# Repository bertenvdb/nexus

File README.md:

# Nexus

**Nexus Tools Board** and **Nexus Docks Board**: Klipper controller boards for a hotend changer with up to 8 tools.

- **Nexus Tools Board:** 8 heaters, 8 thermistors (NTC 100K / PT1000), 8 filament sensors, 1 WS2812 chain, hardware cutoff of the heater rail with startup self-test, USB + CAN.
- **Nexus Docks Board:** 9 fans (5/12/24V), 1 WS2812 chain, USB + CAN.

Both boards: STM32G0B1RBT6, Klipper + Katapult, designed in KiCad 10 for JLCPCB assembly.

Status and documentation: [`docs/README.md`](docs/README.md). Klipper configuration and macros (YUDX toolchanger): [`klipper/`](klipper/README.md). Working agreements for Claude Code: [`CLAUDE.md`](CLAUDE.md).

---

## ⚠️ Safety — read this before you build or use a board

This board drives heaters. A mistake in the design, assembly, wiring or configuration can cause a **fire**. This is a hobby project. It is **not certified**, not CE marked and not independently tested.

**Design limits**
- **24 V DC** only. Max. **70 W per heater channel** (measured at room temperature), max. 8 channels.
- Thermistors: NTC 100K or PT1000. No thermocouples or PT100.
- Only for use with **Klipper** and the included safety macros.

**Mandatory**
1. Klipper's `verify_heater` active, with sensible `max_temp` values.
2. Keep the **cutoff startup self-test** enabled (runs at every Klipper start, `NEXUS_SELFTEST`). Do not print if it fails; call `NEXUS_PRINT_START` in your `PRINT_START` so a print cannot start without it.
3. Run the **commissioning macro** `NEXUS_COMMISSION` after every (re)wiring. It checks that each heater heats the correct thermistor.
4. **Never print unattended** until the whole setup has proven itself over multiple prints.
5. One PSU, or PSUs with a common negative.
6. Check the **power cable polarity** before you plug in: on the board connector (XT60 on the Tools Board, XT30 on the Docks Board) **+ is pin 2**, marked **+** on the silkscreen. Wire your plug to match.

**Optional**
- Extra passive protection at the hotend: a PTC heater (self-limiting) and/or a thermal fuse (TCO) on the heatsink or tool holder. A TCO on the heater block itself does not work: they go up to ±240 °C, at or below print temperature.
- A smoke detector above the printer.

You build and use this design **entirely at your own risk**. See the disclaimers in the licenses.

---

## Licenses

| Part | License |
|---|---|
| Hardware (KiCad files, production files) | [CERN-OHL-S-2.0](LICENSES/CERN-OHL-S-2.0.txt) |
| Klipper macros, config, scripts | [GPL-3.0-or-later](LICENSES/GPL-3.0-or-later.txt) |
| Documentation | [CC-BY-SA-4.0](LICENSES/CC-BY-SA-4.0.txt) |

Copyright © 2026 Berten.

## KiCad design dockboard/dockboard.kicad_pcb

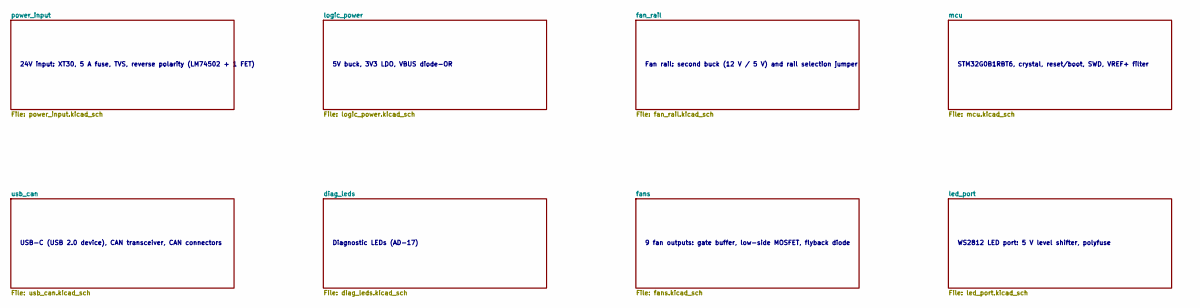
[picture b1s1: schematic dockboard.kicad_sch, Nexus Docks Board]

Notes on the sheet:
USB-C (USB 2.0 device), CAN transceiver, CAN connectors
9 fan outputs: gate buffer, low-side MOSFET, flyback diode
24V input: XT30, 5 A fuse, TVS, reverse polarity (LM74502 + 1 FET)
Diagnostic LEDs (AD-17)
Fan rail: second buck (12 V / 5 V) and rail selection jumper
WS2812 LED port: 5 V level shifter, polyfuse
STM32G0B1RBT6, crystal, reset/boot, SWD, VREF+ filter
5V buck, 3V3 LDO, VBUS diode-OR

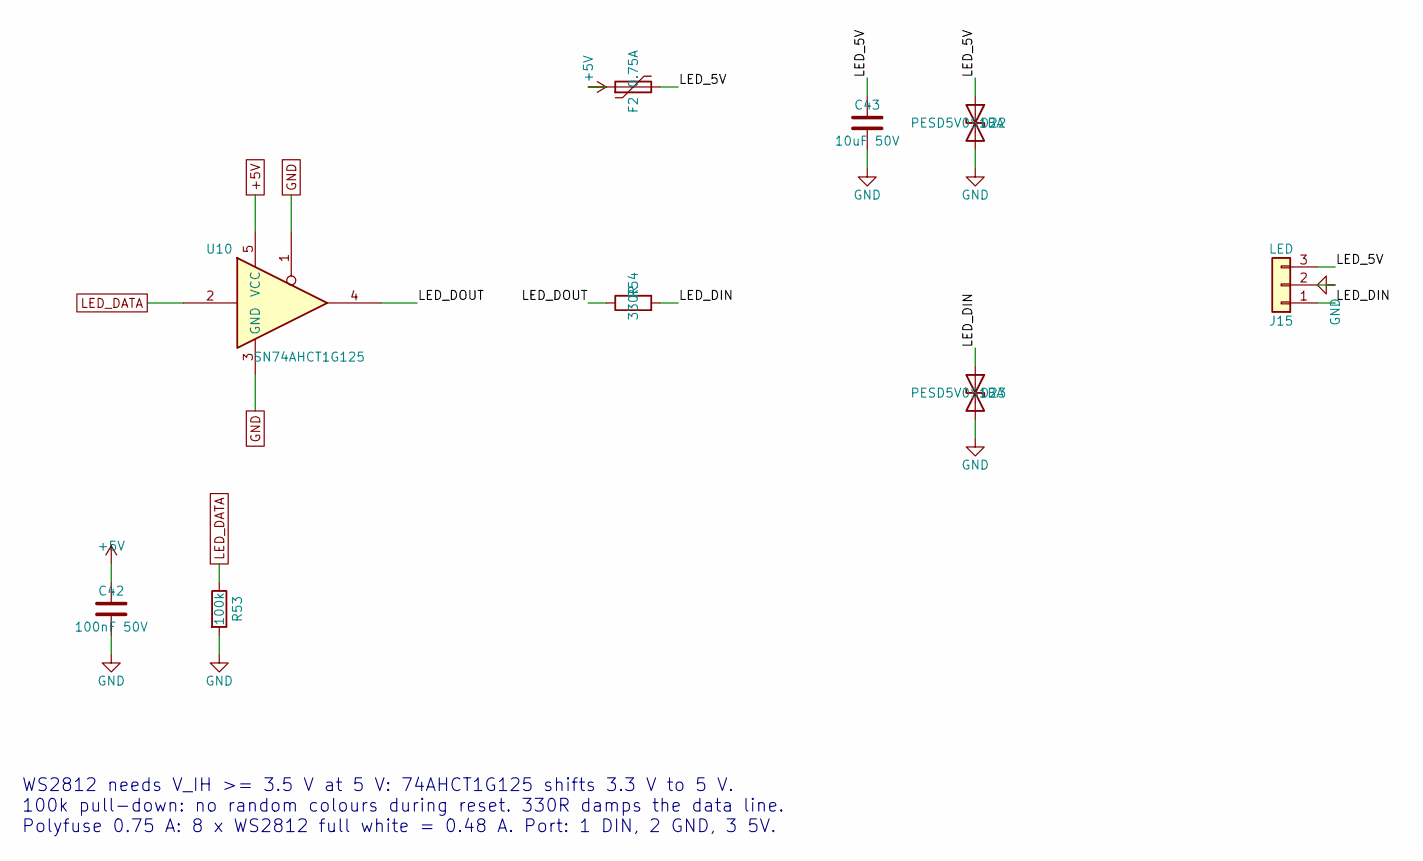
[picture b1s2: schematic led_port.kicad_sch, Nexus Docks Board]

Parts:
C42: 100nF 50V; C_0603_1608Metric; MPN CC0603KRX7R9BB104; LCSC C14663
C43: 10uF 50V; C_1206_3216Metric; MPN CL31A106KBHNNNE; LCSC C13585
D22, D23: PESD5V0S1BA; D_SOD-323; MPN PESD5V0S1BA; LCSC C2827694
F2: 0.75A; Fuse_1206_3216Metric; MPN JK-nSMD075-16; LCSC C409806
J15: LED; JST_XH_B3B-XH-A_1x03_P2.50mm_Vertical; MPN B3B-XH-A(LF)(SN); LCSC C144394
R53: 100k; R_0603_1608Metric; MPN 0603WAF1003T5E; LCSC C25803
R54: 330R; R_0603_1608Metric; MPN 0603WAF3300T5E; LCSC C23138
U10: SN74AHCT1G125; SOT-23-5; MPN SN74AHCT1G125DBVR; LCSC C7484

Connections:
+5V: C42.1, F2.1, U10.5 (VCC); also elsewhere on the board
/led_port/LED_5V: C43.1, D22.1 (A1), F2.2, J15.3
/led_port/LED_DIN: D23.1 (A1), J15.1, R54.2
/led_port/LED_DOUT: R54.1, U10.4
GND: C42.2, C43.2, D22.2 (A2), D23.2 (A2), J15.2, R53.2, U10.1, U10.3 (GND); also elsewhere on the board
LED_DATA: R53.1, U10.2; also elsewhere on the board

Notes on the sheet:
WS2812 needs V_IH >= 3.5 V at 5 V: 74AHCT1G125 shifts 3.3 V to 5 V. 100k pull-down: no random colours during reset. 330R damps the data line. Polyfuse 0.75 A: 8 x WS2812 full white = 0.48 A. Port: 1 DIN, 2 GND, 3 5V.

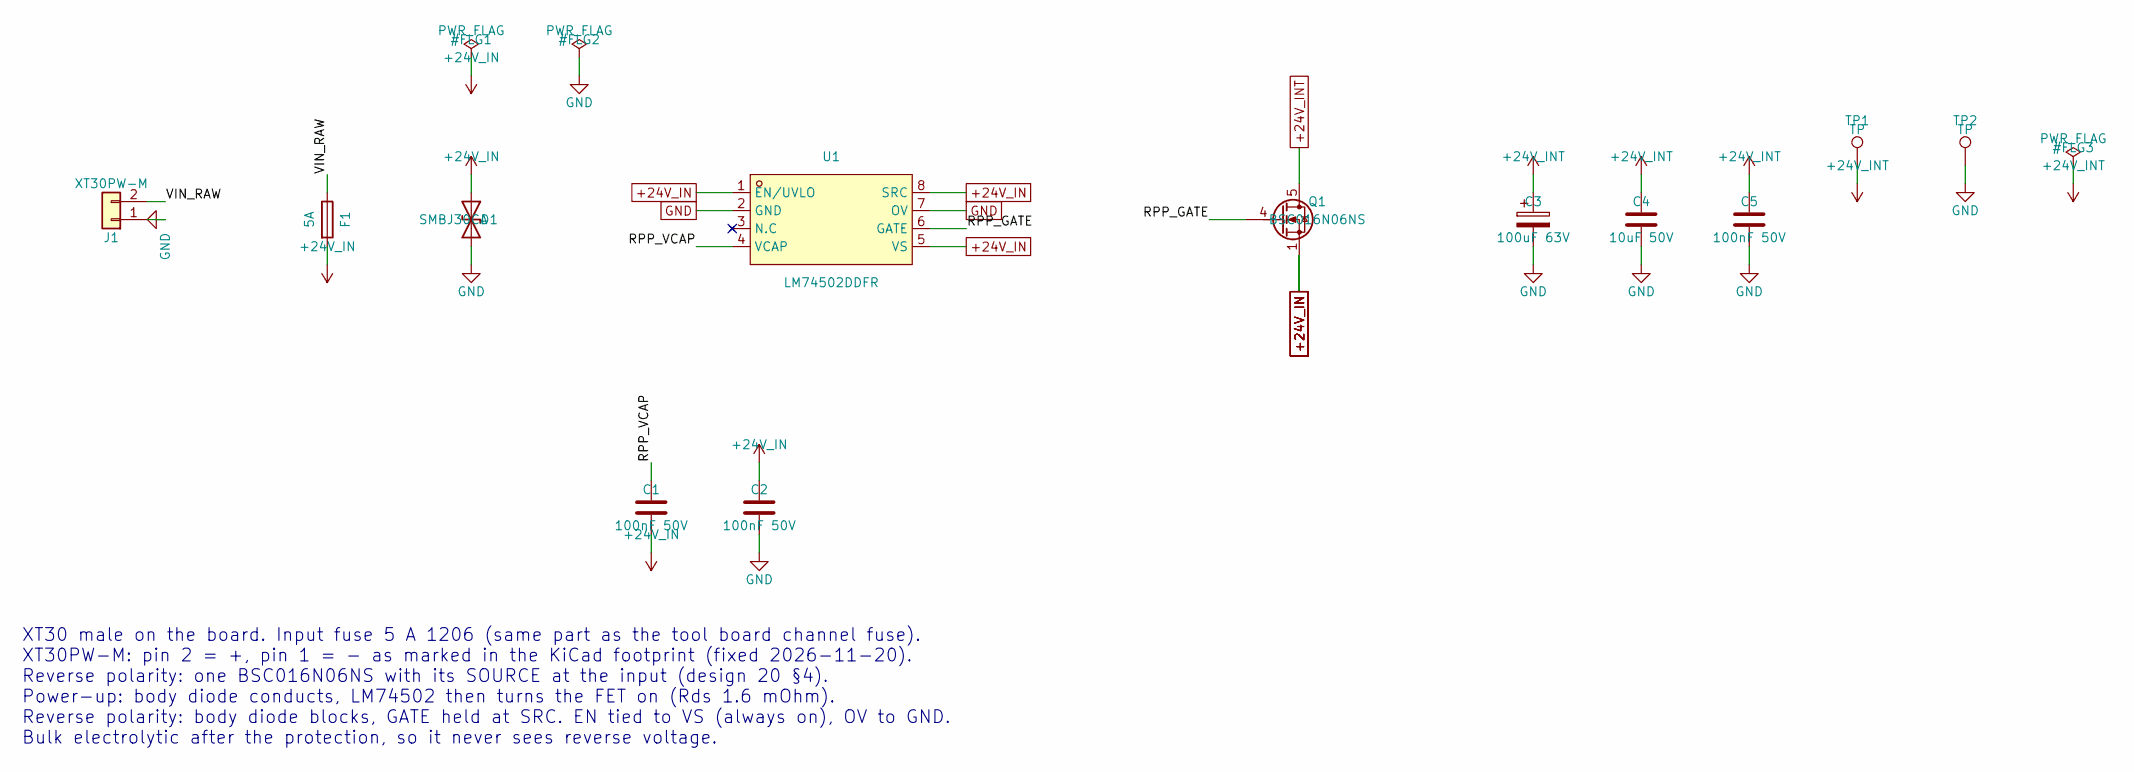
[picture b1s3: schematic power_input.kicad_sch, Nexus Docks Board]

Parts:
C1, C2, C5: 100nF 50V; C_0603_1608Metric; MPN CC0603KRX7R9BB104; LCSC C14663
C3: 100uF 63V; CP_Radial_D8.0mm_P3.50mm; MPN 63ZLH100MEFC8X16; LCSC C88747
C4: 10uF 50V; C_1206_3216Metric; MPN CL31A106KBHNNNE; LCSC C13585
D1: SMBJ30CA; D_SMB; MPN SMBJ30CA; LCSC C2925441
F1: 5A; Fuse_1206_3216Metric; MPN 0466005.NRHF; LCSC C57525
J1: XT30PW-M; AMASS_XT30PW-M_1x02_P2.50mm_Horizontal; MPN XT30PW-M30.G.Y; LCSC C431092
Q1: BSC016N06NS; Infineon_PG-TDSON-8_6.15x5.15mm; MPN BSC016N06NS; LCSC C454269
TP1, TP2: TP; TestPoint_Pad_D1.0mm
U1: LM74502DDFR; TSOT-23-8; MPN LM74502DDFR; LCSC C3236215

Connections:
+24V_IN: C1.2, C2.1, D1.1 (A1), F1.2, Q1.1 (S), Q1.2 (S), Q1.3 (S), U1.1 (EN/UVLO), U1.5 (VS), U1.8 (SRC)
+24V_INT: C3.1, C4.1, C5.1, Q1.5 (D), TP1.1; also elsewhere on the board
/power_input/RPP_GATE: Q1.4 (G), U1.6 (GATE)
/power_input/RPP_VCAP: C1.1, U1.4 (VCAP)
/power_input/VIN_RAW: F1.1, J1.2
GND: C2.2, C3.2, C4.2, C5.2, D1.2 (A2), J1.1, TP2.1, U1.2 (GND), U1.7 (OV); also elsewhere on the board

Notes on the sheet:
XT30 male on the board. Input fuse 5 A 1206 (same part as the tool board channel fuse). XT30PW-M: pin 2 = +, pin 1 = - as marked in the KiCad footprint (fixed 2026-11-20). Reverse polarity: one BSC016N06NS with its SOURCE at the input (design 20 §4). Power-up: body diode conducts, LM74502 then turn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

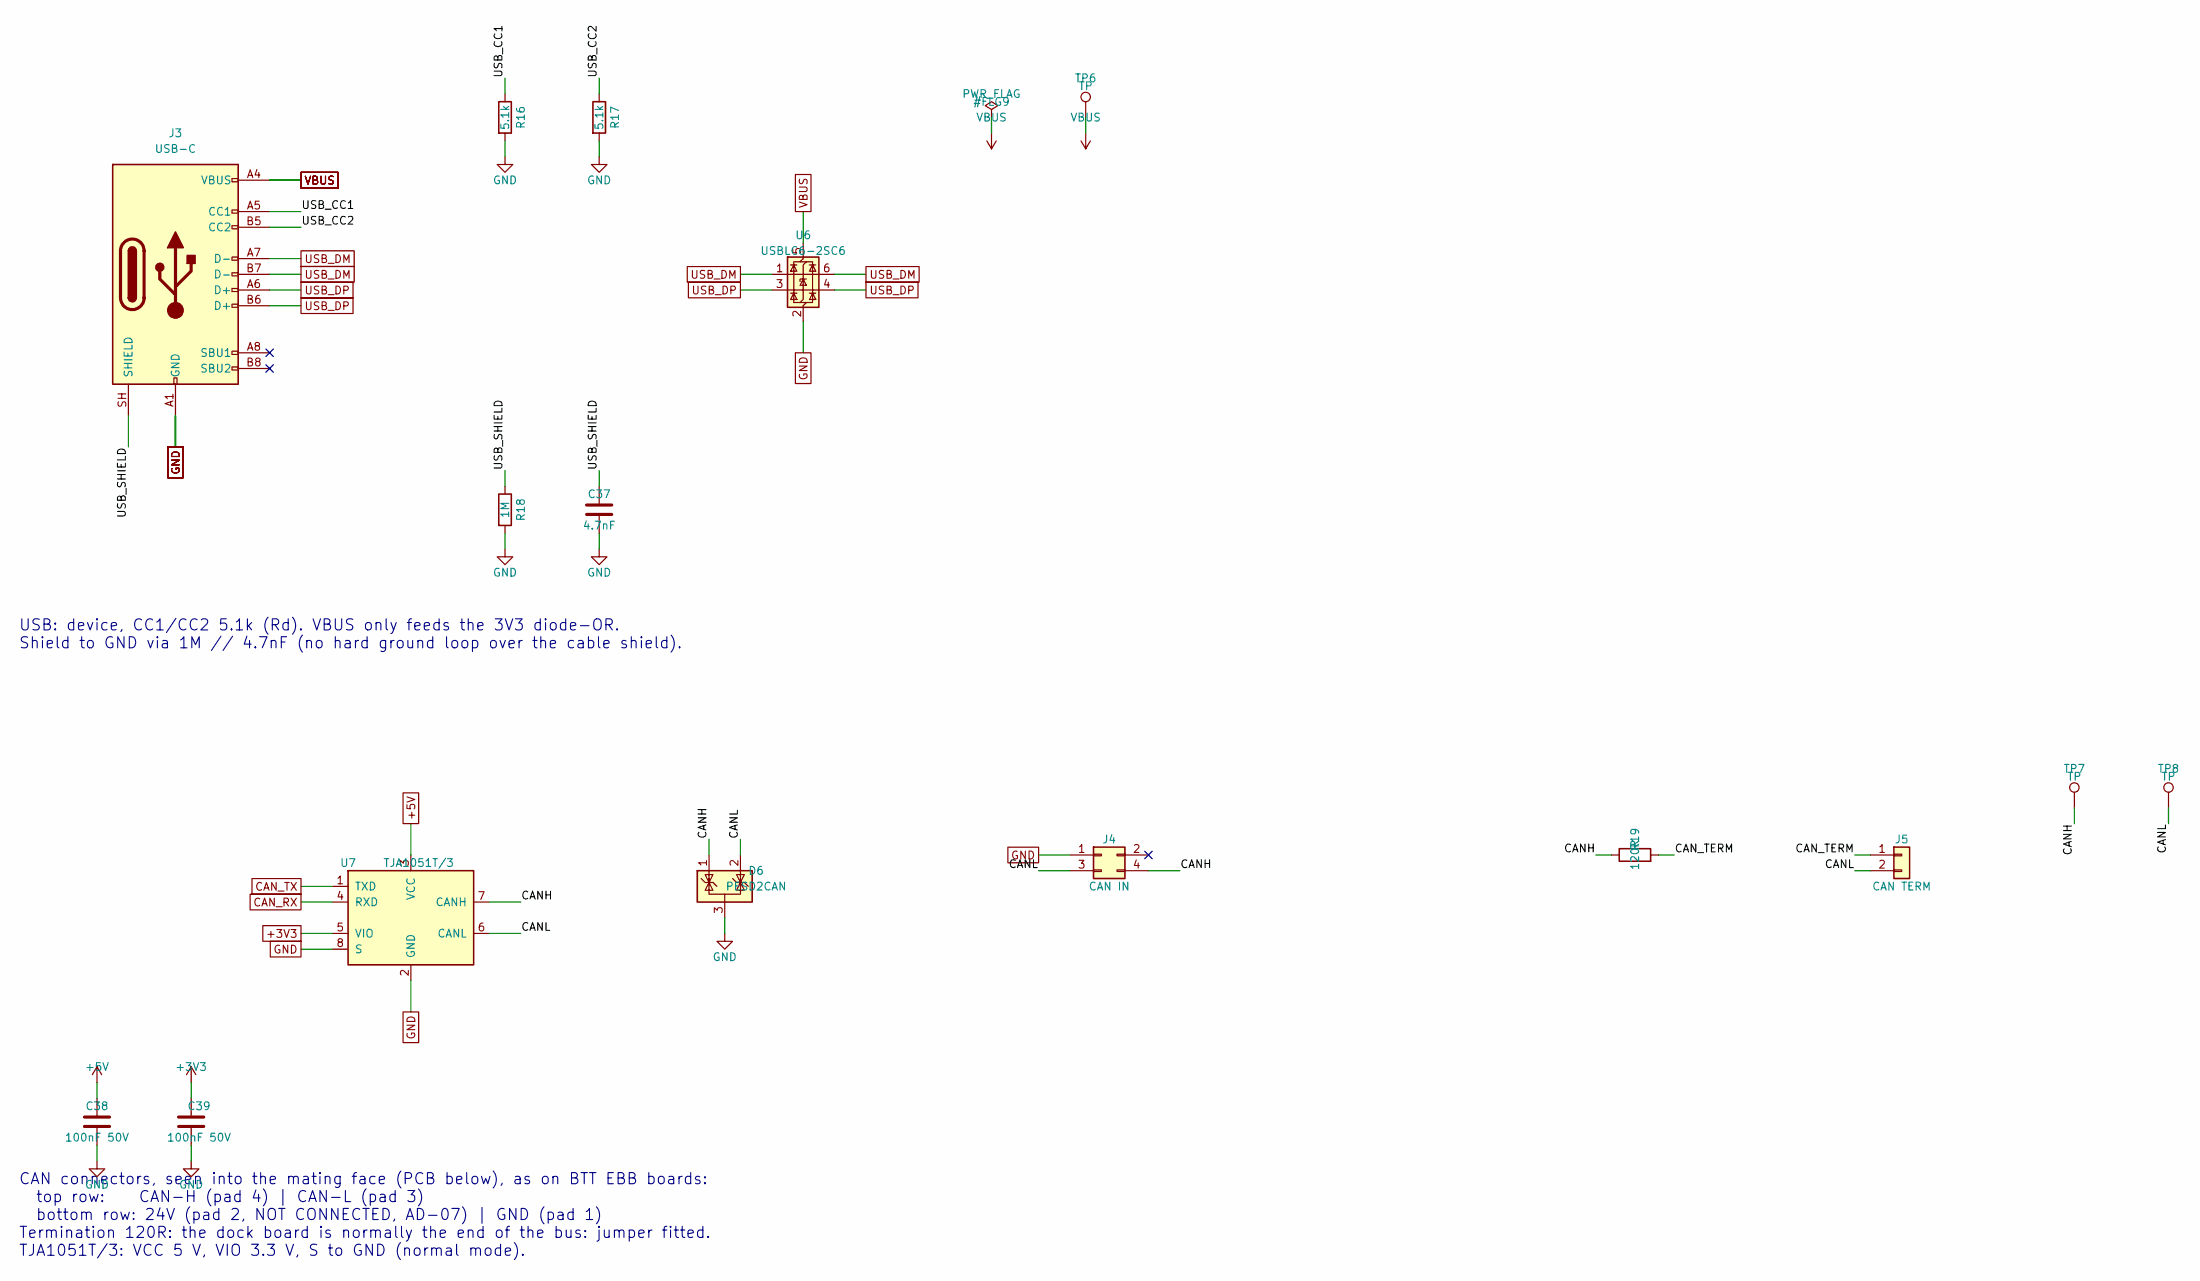
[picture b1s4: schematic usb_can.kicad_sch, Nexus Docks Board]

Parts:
C37: 4.7nF; C_0603_1608Metric; MPN 0603B472K500NT; LCSC C53987
C38, C39: 100nF 50V; C_0603_1608Metric; MPN CC0603KRX7R9BB104; LCSC C14663
D6: PESD2CAN; SOT-23; MPN PESD2CAN; LCSC C907830
J3: USB-C; USB_C_Receptacle_HRO_TYPE-C-31-M-12; MPN TYPE-C-31-M-12; LCSC C165948
J4: CAN IN; Molex_Micro-Fit_3.0_43045-0400_2x02_P3.00mm_Horizontal; MPN 43045-0400; LCSC C122413
J5: CAN TERM; PinHeader_1x02_P2.54mm_Vertical; MPN PZ254V-11-02P; LCSC C492401
R16, R17: 5.1k; R_0603_1608Metric; MPN 0603WAF5101T5E; LCSC C23186
R18: 1M; R_0603_1608Metric; MPN 0603WAF1004T5E; LCSC C22935
R19: 120R; R_0603_1608Metric; MPN 0603WAF1200T5E; LCSC C22787
TP6, TP7, TP8: TP; TestPoint_Pad_D1.5mm
U6: USBLC6-2SC6; SOT-23-6; MPN USBLC6-2SC6; LCSC C7519
U7: TJA1051T/3; SOIC-8_3.9x4.9mm_P1.27mm; MPN TJA1051T/3/1J; LCSC C38695

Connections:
+3V3: C39.1, U7.5 (VIO); also elsewhere on the board
+5V: C38.1, U7.3 (VCC); also elsewhere on the board
/usb_can/CANH: D6.1 (K), J4.4, R19.1, TP7.1, U7.7 (CANH)
/usb_can/CANL: D6.2 (K), J4.3, J5.2, TP8.1, U7.6 (CANL)
/usb_can/CAN_TERM: J5.1, R19.2
/usb_can/USB_CC1: J3.A5 (CC1), R16.1
/usb_can/USB_CC2: J3.B5 (CC2), R17.1
/usb_can/USB_SHIELD: C37.1, J3.SH (SHIELD), R18.1
CAN_RX: U7.4 (RXD); also elsewhere on the board
CAN_TX: U7.1 (TXD); also elsewhere on the board
GND: C37.2, C38.2, C39.2, D6.3 (A), J3.A1 (GND), J3.A12 (GND), J3.B1 (GND), J3.B12 (GND), J4.1, R16.2, R17.2, R18.2, U6.2 (GND), U7.2 (GND), U7.8 (S); also elsewhere on the board
USB_DM: J3.A7 (D-), J3.B7 (D-), U6.1 (I/O1), U6.6 (I/O1); also elsewhere on the board
USB_DP: J3.A6 (D+), J3.B6 (D+), U6.3 (I/O2), U6.4 (I/O2); also elsewhere on the board
VBUS: J3.A4 (VBUS), J3.A9 (VBUS), J3.B4 (VBUS), J3.B9 (VBUS), TP6.1, U6.5 (VBUS); also elsewhere on the board

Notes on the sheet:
USB: device, CC1/CC2 5.1k (Rd). VBUS only feeds the 3V3 diode-OR. Shield to GND via 1M // 4.7nF (no hard ground loop over the cable shield).
CAN connectors, seen into the mating face (PCB below), as on BTT EBB boards: top row: CAN-H (pad 4) | CAN-L (pad 3) bottom row: 24V (pad 2, NOT CONNECTED, AD-07) | GND (pad 1) Termination 120R: the dock board is normally the end of the bus: jumper fitted. TJA1051T/3: VCC 5 V, VIO 3.3 V, S to GND (n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

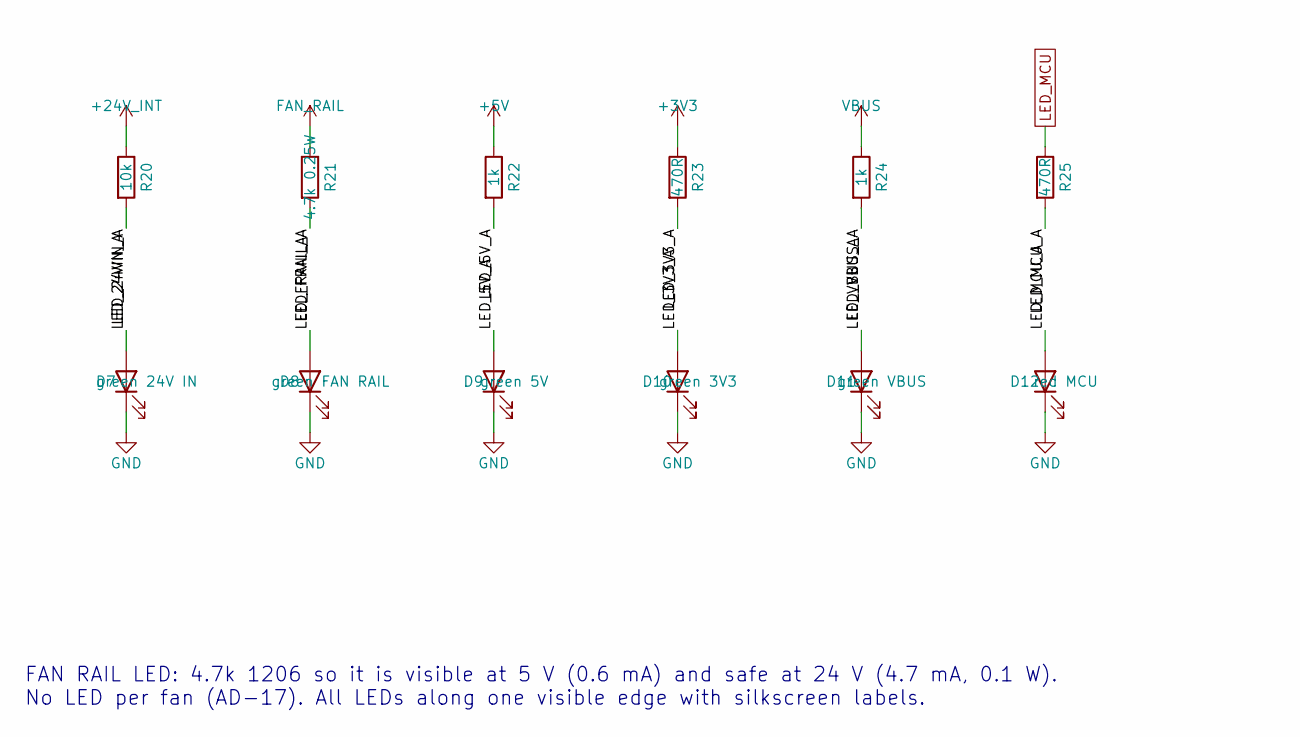
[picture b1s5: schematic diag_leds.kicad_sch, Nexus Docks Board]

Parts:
D7: green 24V IN; LED_0805_2012Metric; MPN KT-0805G; LCSC C2297
D8: green FAN RAIL; LED_0805_2012Metric; MPN KT-0805G; LCSC C2297
D9: green 5V; LED_0805_2012Metric; MPN KT-0805G; LCSC C2297
D10: green 3V3; LED_0805_2012Metric; MPN KT-0805G; LCSC C2297
D11: green VBUS; LED_0805_2012Metric; MPN KT-0805G; LCSC C2297
D12: red MCU; LED_0603_1608Metric; MPN KT-0603R; LCSC C2286
R20: 10k; R_0603_1608Metric; MPN 0603WAF1002T5E; LCSC C25804
R21: 4.7k 0.25W; R_1206_3216Metric; MPN 1206W4F4701T5E; LCSC C17936
R22, R24: 1k; R_0603_1608Metric; MPN 0603WAF1001T5E; LCSC C21190
R23, R25: 470R; R_0603_1608Metric; MPN 0603WAF4700T5E; LCSC C23179

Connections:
+3V3: R23.1; also elsewhere on the board
+5V: R22.1; also elsewhere on the board
+24V_INT: R20.1; also elsewhere on the board
/diag_leds/LED_3V3_A: D10.2 (A), R23.2
/diag_leds/LED_5V_A: D9.2 (A), R22.2
/diag_leds/LED_24VIN_A: D7.2 (A), R20.2
/diag_leds/LED_FRAIL_A: D8.2 (A), R21.2
/diag_leds/LED_MCU_A: D12.2 (A), R25.2
/diag_leds/LED_VBUS_A: D11.2 (A), R24.2
FAN_RAIL: R21.1; also elsewhere on the board
GND: D7.1 (K), D8.1 (K), D9.1 (K), D10.1 (K), D11.1 (K), D12.1 (K); also elsewhere on the board
LED_MCU: R25.1; also elsewhere on the board
VBUS: R24.1; also elsewhere on the board

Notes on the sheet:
FAN RAIL LED: 4.7k 1206 so it is visible at 5 V (0.6 mA) and safe at 24 V (4.7 mA, 0.1 W). No LED per fan (AD-17). All LEDs along one visible edge with silkscreen labels.

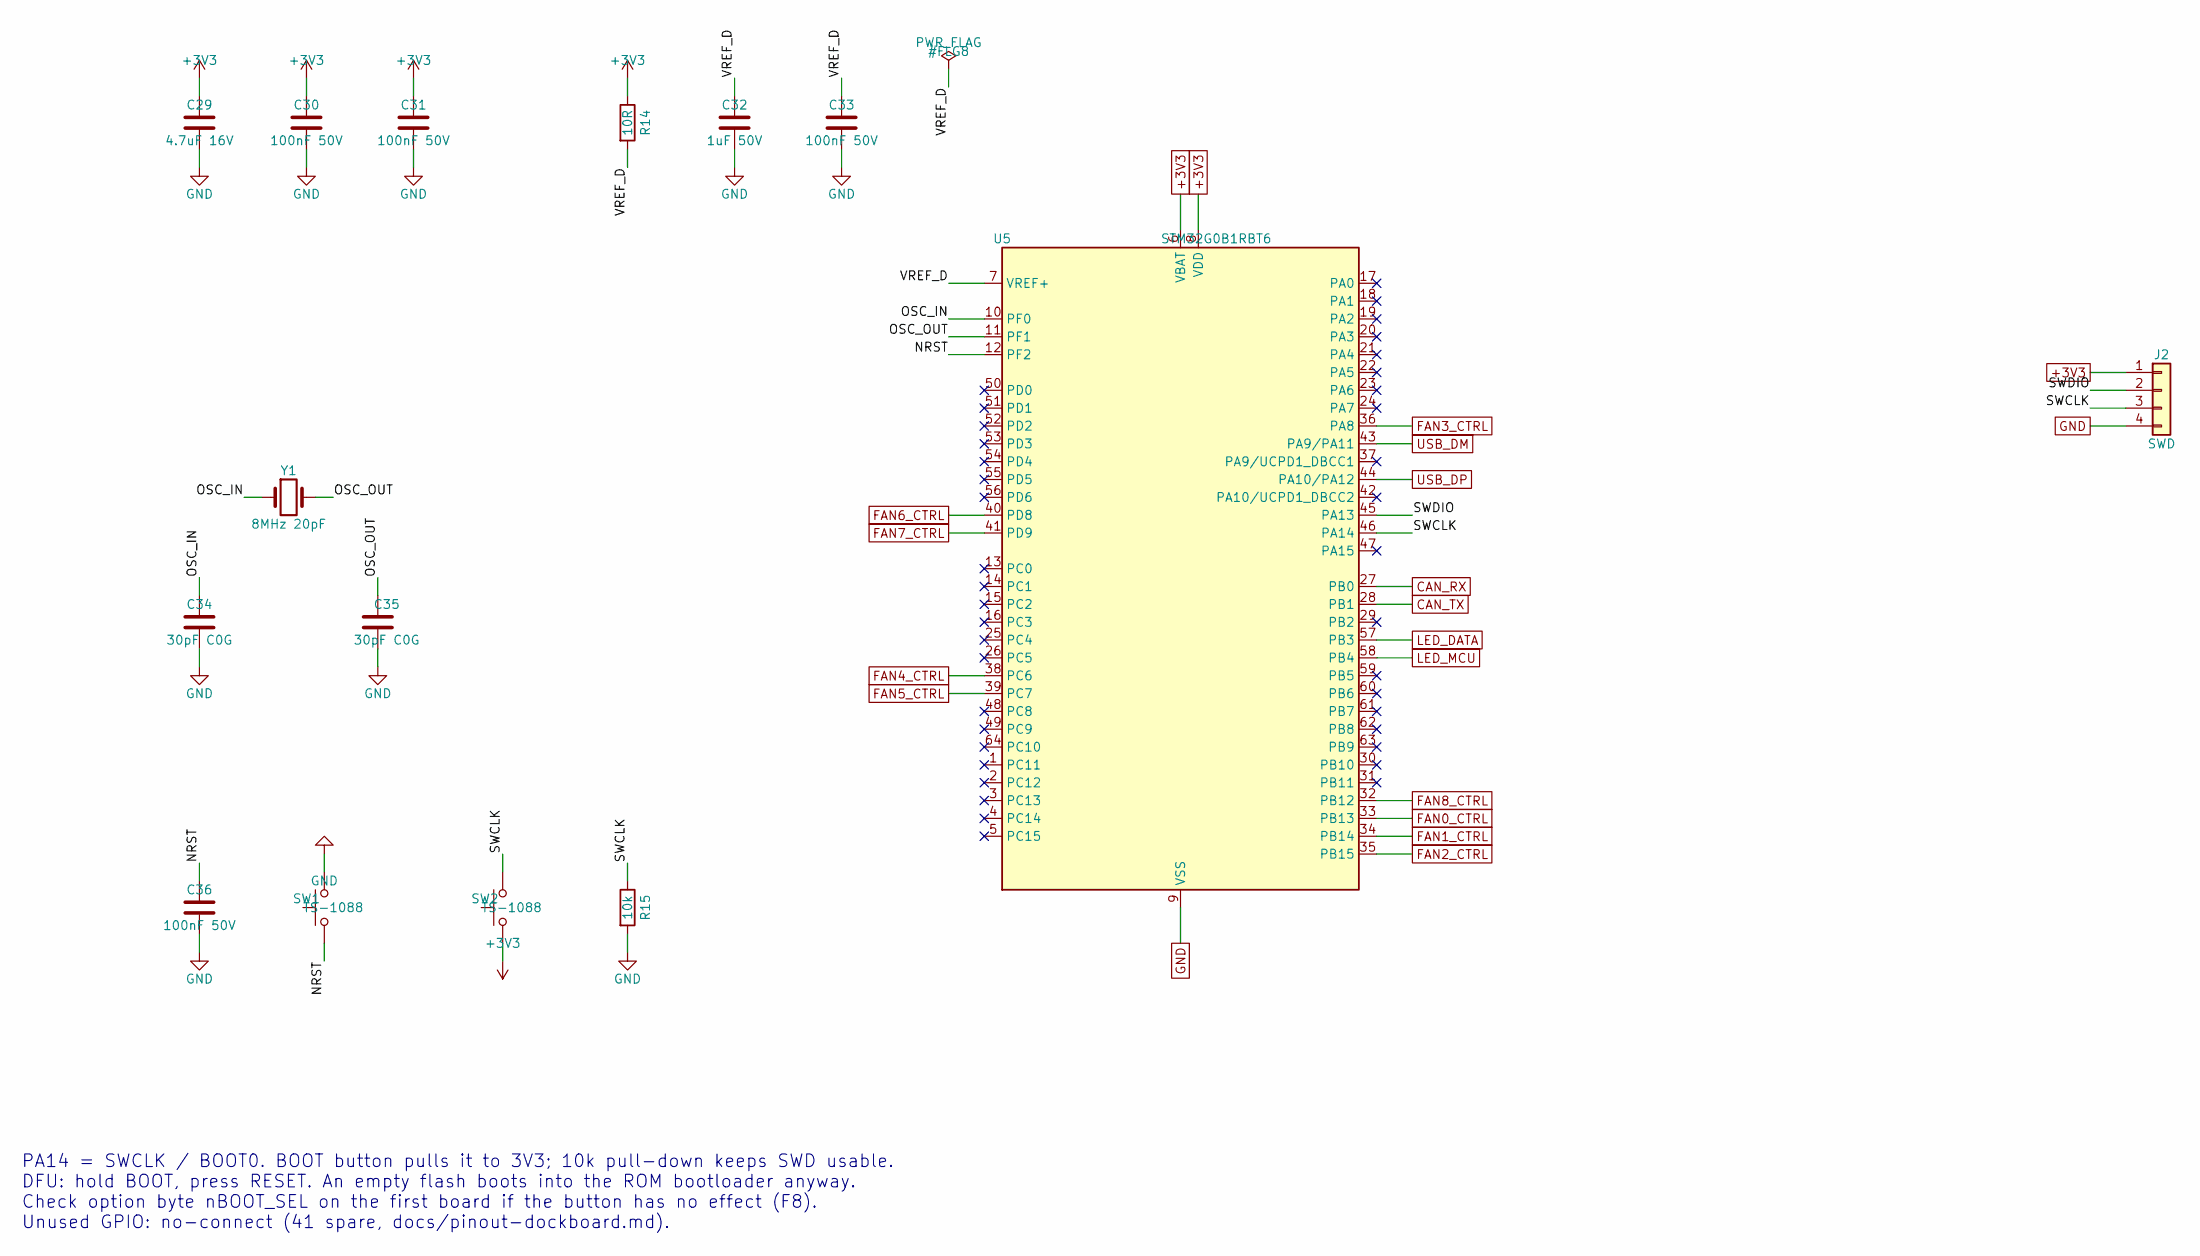
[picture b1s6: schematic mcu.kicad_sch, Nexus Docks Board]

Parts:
C29: 4.7uF 16V; C_0603_1608Metric; MPN CL10A475KO8NNNC; LCSC C19666
C30, C31, C33, C36: 100nF 50V; C_0603_1608Metric; MPN CC0603KRX7R9BB104; LCSC C14663
C32: 1uF 50V; C_0603_1608Metric; MPN CL10A105KB8NNNC; LCSC C15849
C34, C35: 30pF C0G; C_0603_1608Metric; MPN 0603CG300J500NT; LCSC C1658
J2: SWD; PinHeader_1x04_P2.54mm_Vertical; MPN HX PZ2.54-1x4P ZZ; LCSC C32713270
R14: 10R; R_0603_1608Metric; MPN 0603WAF100JT5E; LCSC C22859
R15: 10k; R_0603_1608Metric; MPN 0603WAF1002T5E; LCSC C25804
SW1, SW2: TS-1088; SW_SPST_TS-1088-xR020; MPN TS-1088-AR02016; LCSC C720477
U5: STM32G0B1RBT6; LQFP-64_10x10mm_P0.5mm; MPN STM32G0B1RBT6; LCSC C5143679
Y1: 8MHz 20pF; Crystal_SMD_5032-2Pin_5.0x3.2mm; MPN X50328MSB2GI; LCSC C115962

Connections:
+3V3: C29.1, C30.1, C31.1, J2.1, R14.1, SW2.1, U5.6 (VBAT), U5.8 (VDD); also elsewhere on the board
/mcu/NRST: C36.1, SW1.1, U5.12 (PF2)
/mcu/OSC_IN: C34.1, U5.10 (PF0), Y1.1
/mcu/OSC_OUT: C35.1, U5.11 (PF1), Y1.2
/mcu/SWCLK: J2.3, R15.1, SW2.2, U5.46 (PA14)
/mcu/SWDIO: J2.2, U5.45 (PA13)
/mcu/VREF_D: C32.1, C33.1, R14.2, U5.7 (VREF+)
CAN_RX: U5.27 (PB0); also elsewhere on the board
CAN_TX: U5.28 (PB1); also elsewhere on the board
FAN0_CTRL: U5.33 (PB13); also elsewhere on the board
FAN1_CTRL: U5.34 (PB14); also elsewhere on the board
FAN2_CTRL: U5.35 (PB15); also elsewhere on the board
FAN3_CTRL: U5.36 (PA8); also elsewhere on the board
FAN4_CTRL: U5.38 (PC6); also elsewhere on the board
FAN5_CTRL: U5.39 (PC7); also elsewhere on the board
FAN6_CTRL: U5.40 (PD8); also elsewhere on the board
FAN7_CTRL: U5.41 (PD9); also elsewhere on the board
FAN8_CTRL: U5.32 (PB12); also elsewhere on the board
GND: C29.2, C30.2, C31.2, C32.2, C33.2, C34.2, C35.2, C36.2, J2.4, R15.2, SW1.2, U5.9 (VSS); also elsewhere on the board
LED_DATA: U5.57 (PB3); also elsewhere on the board
LED_MCU: U5.58 (PB4); also elsewhere on the board
USB_DM: U5.43 (PA9/PA11); also elsewhere on the board
USB_DP: U5.44 (PA10/PA12); also elsewhere on the board

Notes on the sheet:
PA14 = SWCLK / BOOT0. BOOT button pulls it to 3V3; 10k pull-down keeps SWD usable. DFU: hold BOOT, press RESET. An empty flash boots into the ROM bootloader anyway. Check option byte nBOOT_SEL on the first board if the button has no effect (F8). Unused GPIO: no-connect (41 spare, docs/pinout-dockbo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

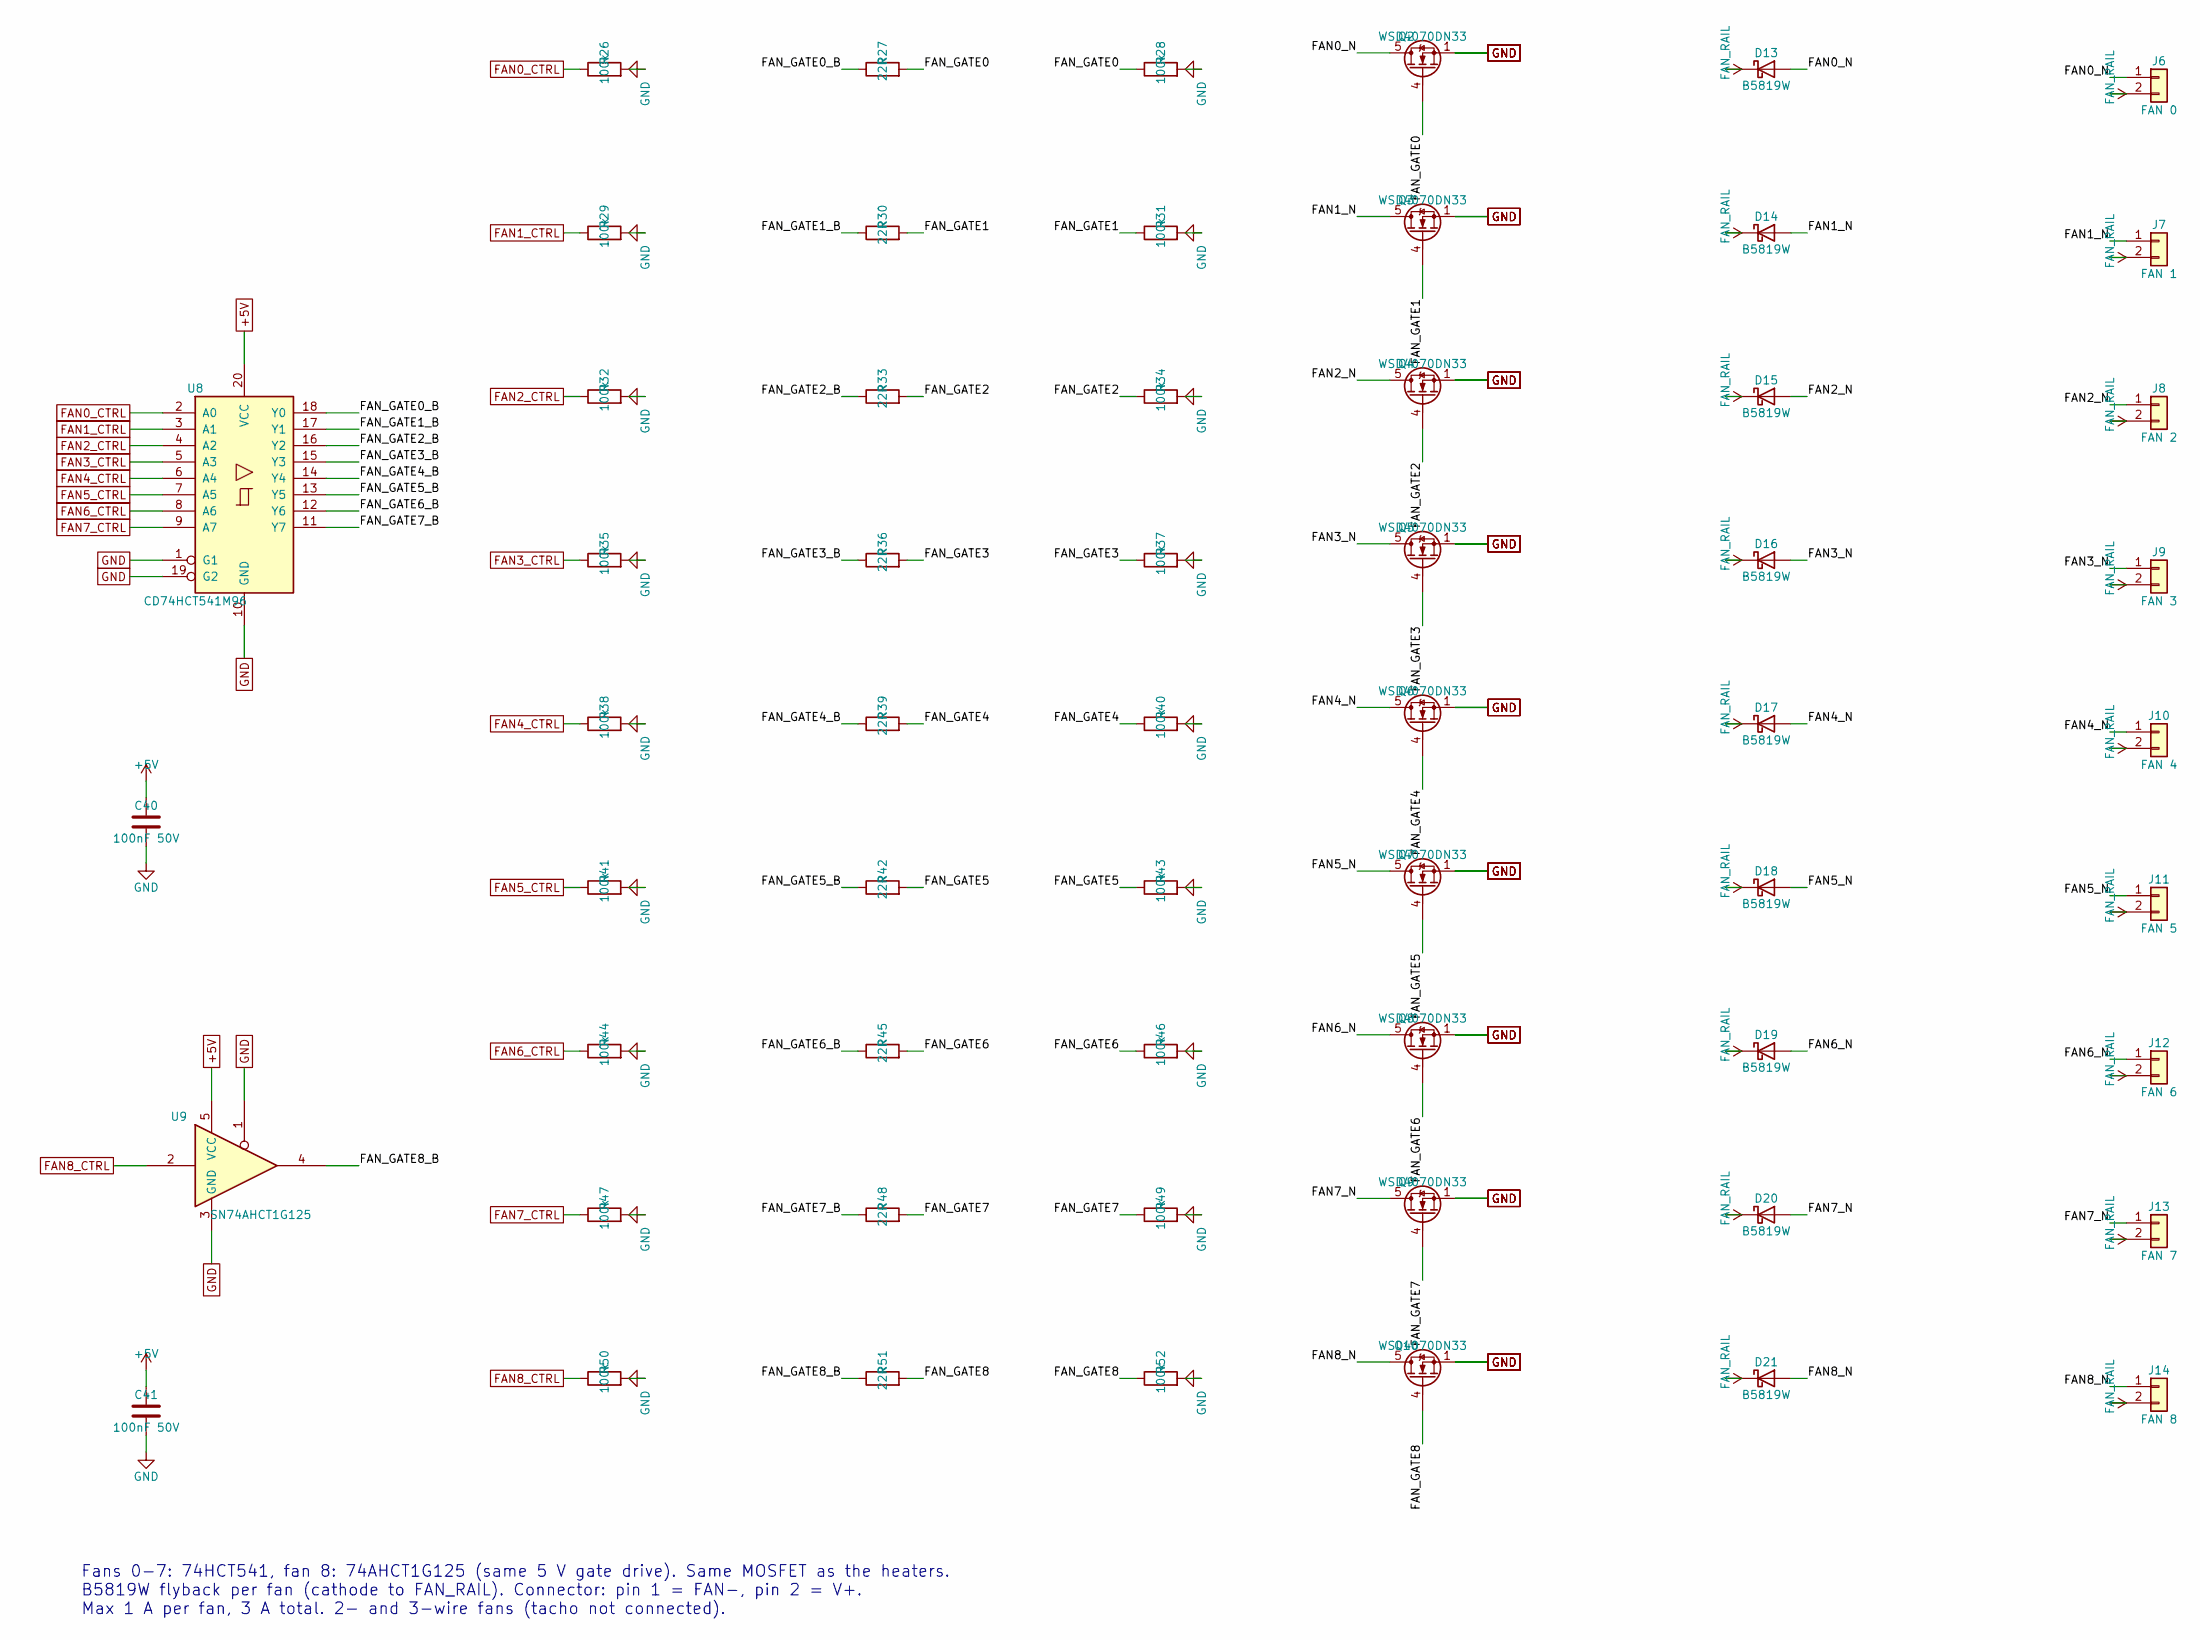
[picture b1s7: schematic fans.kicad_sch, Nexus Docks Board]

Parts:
C40, C41: 100nF 50V; C_0603_1608Metric; MPN CC0603KRX7R9BB104; LCSC C14663
D13, D14, D15, D16, D17, D18, D19, D20, D21: B5819W; D_SOD-123; MPN B5819W SL; LCSC C8598
J6: FAN 0; JST_XH_B2B-XH-A_1x02_P2.50mm_Vertical; MPN B2B-XH-A(LF)(SN); LCSC C158012
J7: FAN 1; JST_XH_B2B-XH-A_1x02_P2.50mm_Vertical; MPN B2B-XH-A(LF)(SN); LCSC C158012
J8: FAN 2; JST_XH_B2B-XH-A_1x02_P2.50mm_Vertical; MPN B2B-XH-A(LF)(SN); LCSC C158012
J9: FAN 3; JST_XH_B2B-XH-A_1x02_P2.50mm_Vertical; MPN B2B-XH-A(LF)(SN); LCSC C158012
J10: FAN 4; JST_XH_B2B-XH-A_1x02_P2.50mm_Vertical; MPN B2B-XH-A(LF)(SN); LCSC C158012
J11: FAN 5; JST_XH_B2B-XH-A_1x02_P2.50mm_Vertical; MPN B2B-XH-A(LF)(SN); LCSC C158012
J12: FAN 6; JST_XH_B2B-XH-A_1x02_P2.50mm_Vertical; MPN B2B-XH-A(LF)(SN); LCSC C158012
J13: FAN 7; JST_XH_B2B-XH-A_1x02_P2.50mm_Vertical; MPN B2B-XH-A(LF)(SN); LCSC C158012
J14: FAN 8; JST_XH_B2B-XH-A_1x02_P2.50mm_Vertical; MPN B2B-XH-A(LF)(SN); LCSC C158012
Q2, Q3, Q4, Q5, Q6, Q7, Q8, Q9, Q10: WSD4070DN33; PDFN3333-8_L3.1-W3.2-P0.65-LS3.4-BL; MPN WSD4070DN33; LCSC C719095
R26, R28, R29, R31, R32, R34, R35, R37, R38, R40, R41, R43, R44, R46, R47, R49, R50, R52: 100k; R_0603_1608Metric; MPN 0603WAF1003T5E; LCSC C25803
R27, R30, R33, R36, R39, R42, R45, R48, R51: 22R; R_0603_1608Metric; MPN 0603WAF220JT5E; LCSC C23345
U8: CD74HCT541M96; SOIC-20W_7.5x12.8mm_P1.27mm; MPN CD74HCT541M96; LCSC C6560
U9: SN74AHCT1G125; SOT-23-5; MPN SN74AHCT1G125DBVR; LCSC C7484

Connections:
+5V: C40.1, C41.1, U8.20 (VCC), U9.5 (VCC); also elsewhere on the board
/fans/FAN0_N: D13.2 (A), J6.1, Q2.5 (D)
/fans/FAN1_N: D14.2 (A), J7.1, Q3.5 (D)
/fans/FAN2_N: D15.2 (A), J8.1, Q4.5 (D)
/fans/FAN3_N: D16.2 (A), J9.1, Q5.5 (D)
/fans/FAN4_N: D17.2 (A), J10.1, Q6.5 (D)
/fans/FAN5_N: D18.2 (A), J11.1, Q7.5 (D)
/fans/FAN6_N: D19.2 (A), J12.1, Q8.5 (D)
/fans/FAN7_N: D20.2 (A), J13.1, Q9.5 (D)
/fans/FAN8_N: D21.2 (A), J14.1, Q10.5 (D)
/fans/FAN_GATE0: Q2.4 (G), R27.2, R28.1
/fans/FAN_GATE0_B: R27.1, U8.18 (Y0)
/fans/FAN_GATE1: Q3.4 (G), R30.2, R31.1
/fans/FAN_GATE1_B: R30.1, U8.17 (Y1)
/fans/FAN_GATE2: Q4.4 (G), R33.2, R34.1
/fans/FAN_GATE2_B: R33.1, U8.16 (Y2)
/fans/FAN_GATE3: Q5.4 (G), R36.2, R37.1
/fans/FAN_GATE3_B: R36.1, U8.15 (Y3)
/fans/FAN_GATE4: Q6.4 (G), R39.2, R40.1
/fans/FAN_GATE4_B: R39.1, U8.14 (Y4)
/fans/FAN_GATE5: Q7.4 (G), R42.2, R43.1
/fans/FAN_GATE5_B: R42.1, U8.13 (Y5)
/fans/FAN_GATE6: Q8.4 (G), R45.2, R46.1
/fans/FAN_GATE6_B: R45.1, U8.12 (Y6)
/fans/FAN_GATE7: Q9.4 (G), R48.2, R49.1
/fans/FAN_GATE7_B: R48.1, U8.11 (Y7)
/fans/FAN_GATE8: Q10.4 (G), R51.2, R52.1
/fans/FAN_GATE8_B: R51.1, U9.4
FAN0_CTRL: R26.1, U8.2 (A0); also elsewhere on the board
FAN1_CTRL: R29.1, U8.3 (A1); also elsewhere on the board
FAN2_CTRL: R32.1, U8.4 (A2); also elsewhere on the board
FAN3_CTRL: R35.1, U8.5 (A3); also elsewhere on the board
FAN4_CTRL: R38.1, U8.6 (A4); also elsewhere on the board
FAN5_CTRL: R41.1, U8.7 (A5); also elsewhere on the board
FAN6_CTRL: R44.1, U8.8 (A6); also elsewhere on the board
FAN7_CTRL: R47.1, U8.9 (A7); also elsewhere on the board
FAN8_CTRL: R50.1, U9.2; also elsewhere on the board
FAN_RAIL: D13.1 (K), D14.1 (K), D15.1 (K), D16.1 (K), D17.1 (K), D18.1 (K), D19.1 (K), D20.1 (K), D21.1 (K), J6.2, J7.2, J8.2, J9.2, J10.2, J11.2, J12.2, J13.2, J14.2; also elsewhere on the board
GND: C40.2, C41.2, Q2.1 (S), Q2.2 (S), Q2.3 (S), Q3.1 (S), Q3.2 (S), Q3.3 (S), Q4.1 (S), Q4.2 (S), Q4.3 (S), Q5.1 (S), Q5.2 (S), Q5.3 (S), Q6.1 (S), Q6.2 (S), Q6.3 (S), Q7.1 (S), Q7.2 (S), Q7.3 (S), Q8.1 (S), Q8.2 (S), Q8.3 (S), Q9.1 (S), Q9.2 (S), Q9.3 (S), Q10.1 (S), Q10.2 (S), Q10.3 (S), R26.2, R28.2, R29.2, R31.2, R32.2, R34.2, R35.2, R37.2, R38.2, R40.2, R41.2, R43.2, R44.2, R46.2, R47.2, R49.2, R50.2, R52.2, U8.1 (G1), U8.10 (GND), U8.19 (G2), U9.1, U9.3 (GND); also elsewhere on the board

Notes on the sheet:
Fans 0-7: 74HCT541, fan 8: 74AHCT1G125 (same 5 V gate drive). Same MOSFET as the heaters. B5819W flyback per fan (cathode to FAN_RAIL). Connector: pin 1 = FAN-, pin 2 = V+. Max 1 A per fan, 3 A total. 2- and 3-wire fans (tacho not connected).
